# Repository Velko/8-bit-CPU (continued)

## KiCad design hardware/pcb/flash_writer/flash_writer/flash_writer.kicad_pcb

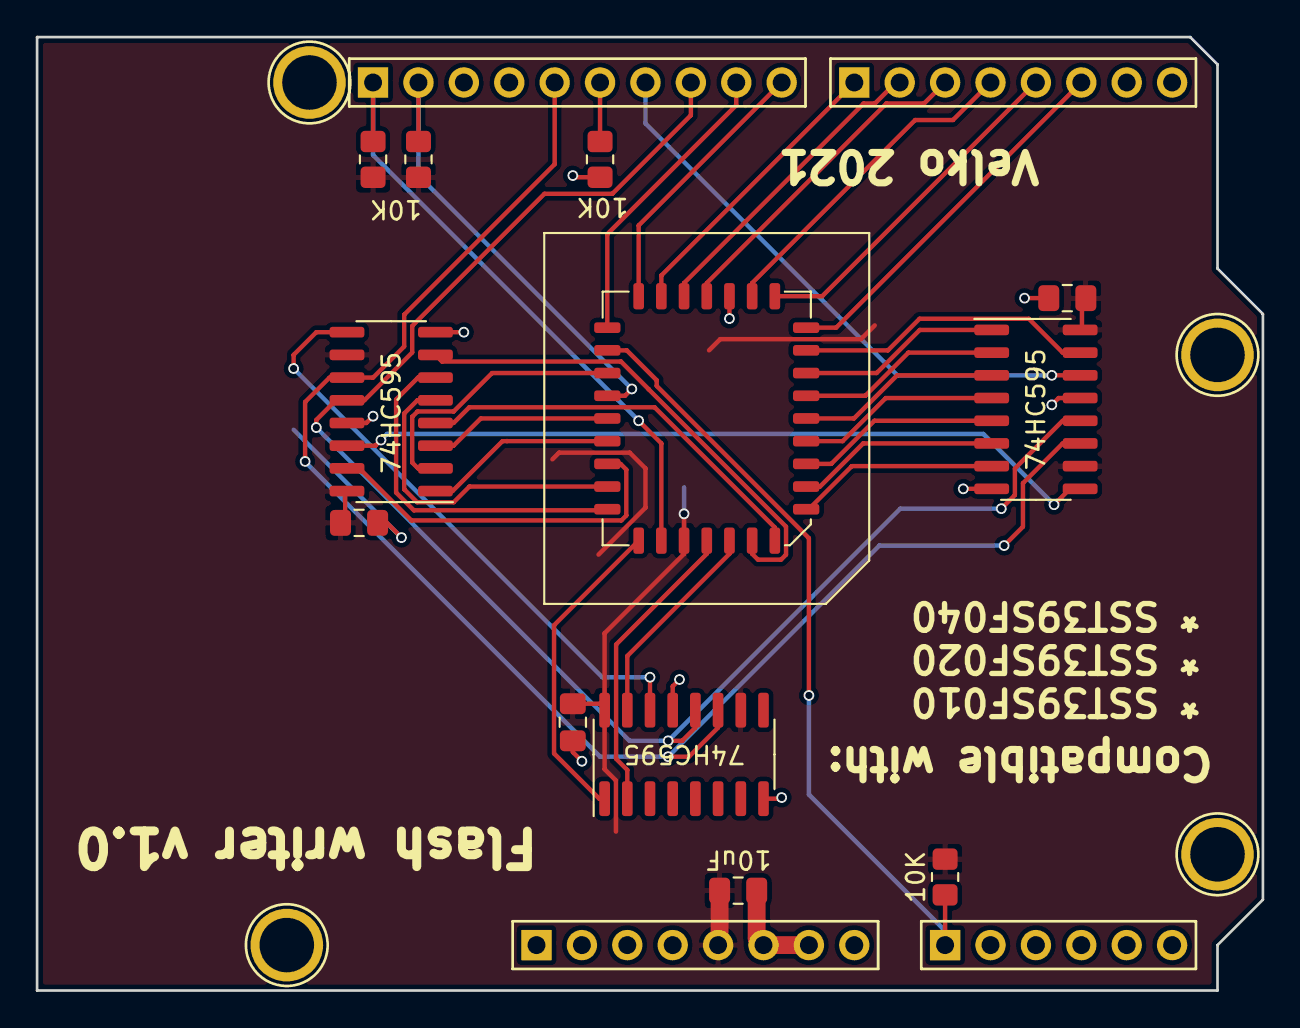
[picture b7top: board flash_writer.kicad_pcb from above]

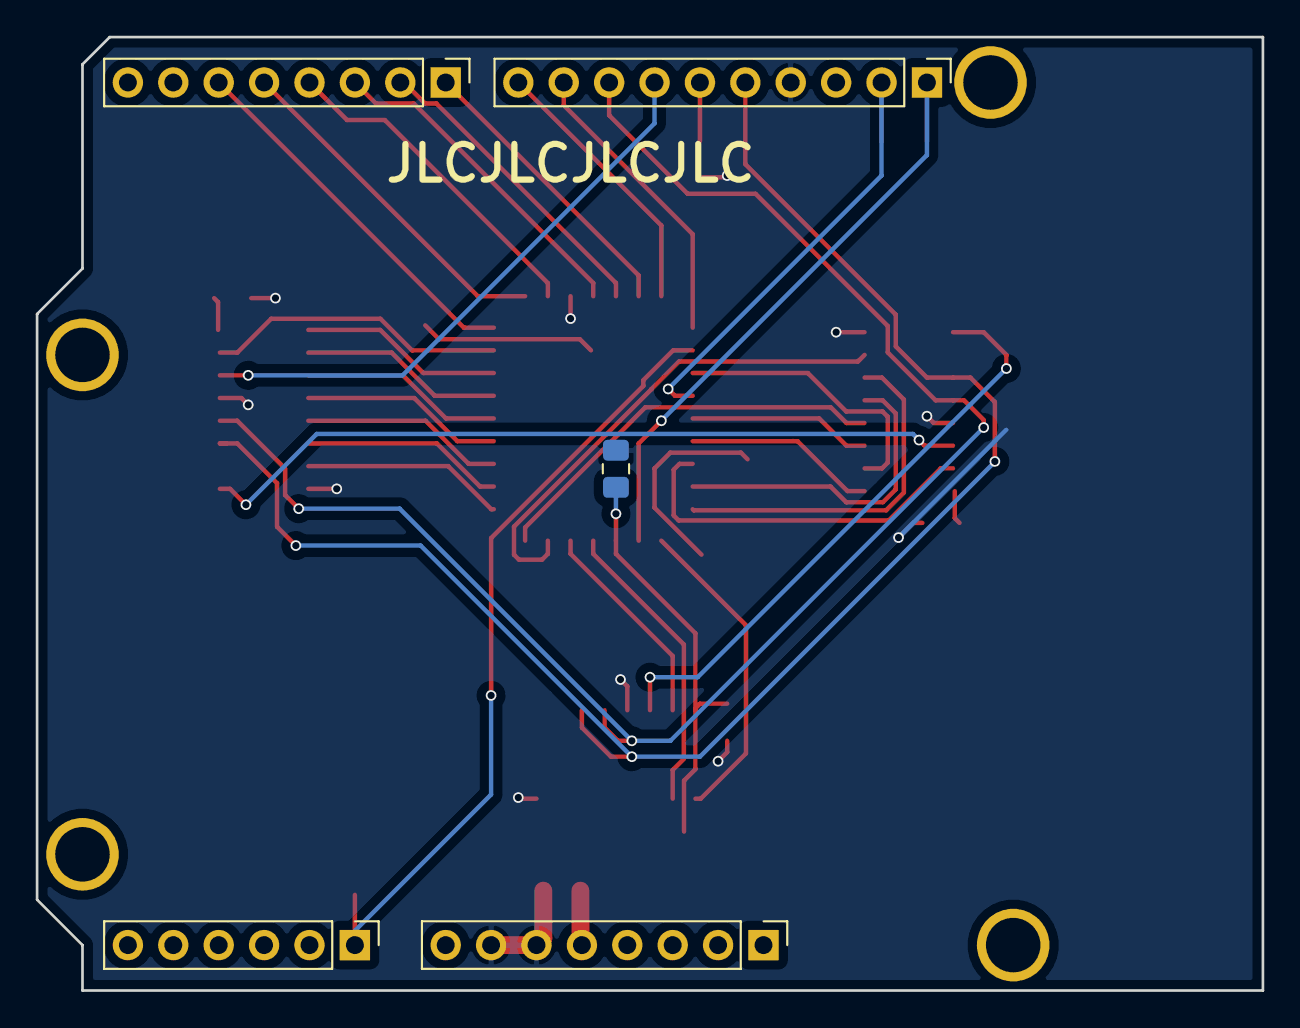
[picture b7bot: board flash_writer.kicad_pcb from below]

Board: 2 copper layers, 68.6 x 53.3 mm, 21 parts (5 on the bottom side), 38 nets.

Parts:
C1, C2, C3, C4: 100nF; C_0805_2012Metric_Pad1.18x1.45mm_HandSolder
C5: 10uF; C_0805_2012Metric_Pad1.18x1.45mm_HandSolder
P1: Power; PinHeader_1x08_P2.54mm_Vertical
P2: Analog; PinHeader_1x06_P2.54mm_Vertical
P3: Digital; PinHeader_1x10_P2.54mm_Vertical
P4: Digital; PinHeader_1x08_P2.54mm_Vertical
P5, P6, P7, P8: CONN_01X01; Arduino_1pin
R1, R2, R3, R4: 10K; R_0805_2012Metric_Pad1.20x1.40mm_HandSolder
U1, U2, U4: 74HC595; SOIC-16_3.9x9.9mm_P1.27mm
U3: SST39SF040; PLCC-32_SMD-Socket

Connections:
+5V: C1.1, C2.1, C3.1, C4.1, C5.1, P1.5, R1.1, R2.1, R4.1, U1.10, U1.16, U2.10, U2.16, U3.32, U4.10, U4.16
A0: U1.15, U3.12
A1: U1.1, U3.11
A2: U1.2, U3.10
A3: U1.3, U3.9
A4: U1.4, U3.8
A5: U1.5, U3.7
A6: U1.6, U3.6
A7: U1.7, U3.5
A8: U2.15, U3.27
A9: U2.1, U3.26
A10: U2.2, U3.23
A11: U2.3, U3.25
A12: U2.4, U3.4
A13: U2.5, U3.28
A14: U2.6, U3.29
A15: U2.7, U3.3
A16: U3.2, U4.15
A17: U3.30, U4.1
A18: U3.1, U4.2
D0: P4.6, U3.13
D1: P4.5, U3.14
D2: P4.4, U3.15
D3: P4.3, U3.17
D4: P4.2, U3.18
D5: P4.1, U3.19
D6: P3.10, U3.20
D7: P3.9, U3.21
GND: C1.2, C2.2, C3.2, C4.2, C5.2, P1.6, P1.7, P3.4, R3.2, U1.8, U1.13, U2.8, U2.13, U3.16, U4.8, U4.13
LATCH: P3.8, U1.12, U2.12, U4.12
MISO: P3.6, R3.1
MOSI: P3.7, U1.14
unnamed: U1.9, U2.14
unnamed: U2.9, U4.14
SCK: P3.5, U1.11, U2.11, U4.11
~CE~: P2.1, R4.2, U3.22
~OE~: P3.2, R1.2, U3.24
~WE~: P3.1, R2.2, U3.31

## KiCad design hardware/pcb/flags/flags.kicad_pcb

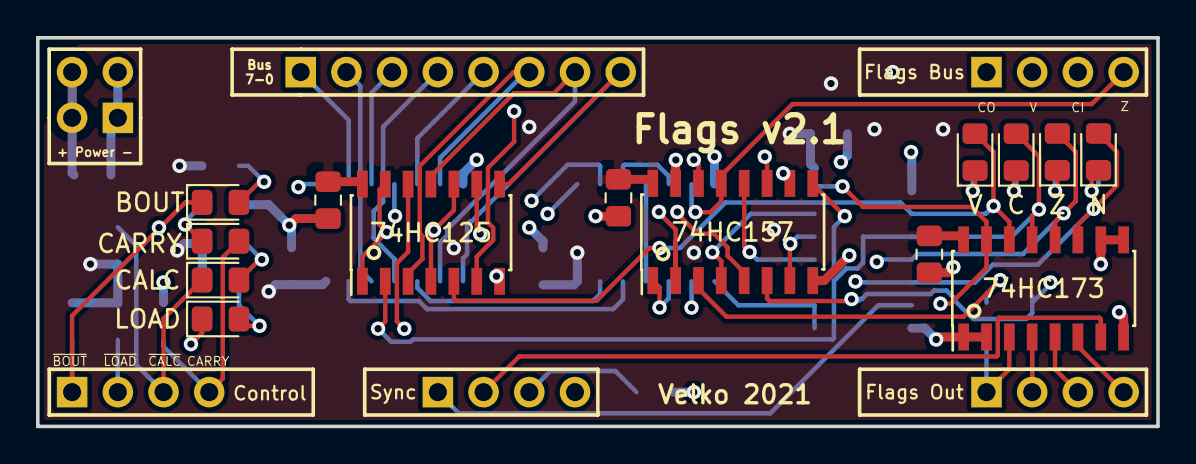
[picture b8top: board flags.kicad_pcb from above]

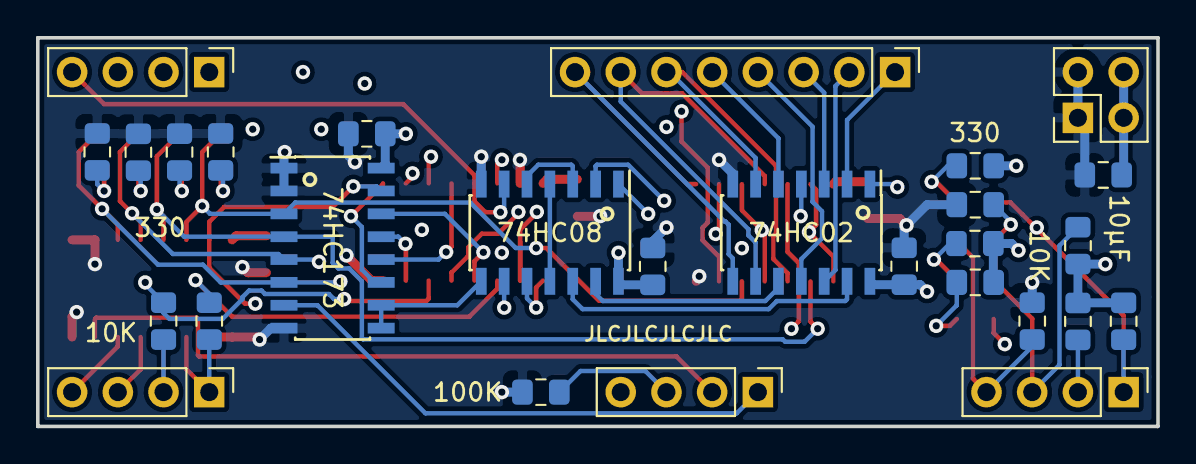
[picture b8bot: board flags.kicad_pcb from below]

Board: 4 copper layers, 62.2 x 21.6 mm, 42 parts (28 on the bottom side), 47 nets.

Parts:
C1, C2, C3, C4, C5, C6: 100nF; C_0805_2012Metric_Pad1.15x1.40mm_HandSolder
C7: 10μF; C_0805_2012Metric_Pad1.15x1.40mm_HandSolder
D1: Z; LED_0805_2012Metric_Pad1.15x1.40mm_HandSolder
D2: V; LED_0805_2012Metric_Pad1.15x1.40mm_HandSolder
D3: N; LED_0805_2012Metric_Pad1.15x1.40mm_HandSolder
D4: C; LED_0805_2012Metric_Pad1.15x1.40mm_HandSolder
D5: LOAD; LED_0805_2012Metric_Pad1.15x1.40mm_HandSolder
D6: BOUT; LED_0805_2012Metric_Pad1.15x1.40mm_HandSolder
D7: CALC; LED_0805_2012Metric_Pad1.15x1.40mm_HandSolder
D8: CARRY; LED_0805_2012Metric_Pad1.15x1.40mm_HandSolder
J1: Bus; PinHeader_1x08_P2.54mm_Vertical
J2: Control; PinHeader_1x04_P2.54mm_Vertical
J3: Sync; PinHeader_1x04_P2.54mm_Vertical
J4: Power; PinHeader_2x02_P2.54mm_Vertical
J5: Flags_Bus; PinHeader_1x04_P2.54mm_Vertical
J6: Ctrl_Out; PinHeader_1x04_P2.54mm_Vertical
R1, R2, R11, R12, R13, R14: 10K; R_0805_2012Metric_Pad1.15x1.40mm_HandSolder
R3, R4, R5, R6, R7, R8, R9, R10: 330; R_0805_2012Metric_Pad1.15x1.40mm_HandSolder
R15: 100K; R_0805_2012Metric_Pad1.15x1.40mm_HandSolder
U1: 74HC02; SOIC-14_3.9x8.7mm_P1.27mm
U2: 74HC08; SOIC-14_3.9x8.7mm_P1.27mm
U3: 74HC157; SOIC-16_3.9x9.9mm_P1.27mm
U4, U5: 74HC173; SOIC-16_3.9x9.9mm_P1.27mm
U6: 74HC125; SOIC-14_3.9x8.7mm_P1.27mm

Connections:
BUS0: J1.8, U1.8, U3.11, U6.8
BUS1: J1.7, U1.9, U3.14, U6.11
BUS2: J1.6, U1.6, U3.5, U6.3
BUS3: J1.5, U1.5, U3.2, U6.6
BUS4: J1.4, U1.11
BUS5: J1.3, U1.3
BUS6: J1.2, U1.12
BUS7: J1.1, U1.2, U3.10
CARRY_IN: J5.3, R1.2, U3.6
CARRY_OUT: D8.2, J2.4, J5.1, R14.2
CLK: J3.1, U4.7
C_CTRL: J6.2, R1.1, U5.4
C_D: D4.2, U4.4, U5.13, U6.2
C_I: U3.7, U4.13
GND: C1.2, C2.2, C3.2, C4.2, C5.2, C6.2, C7.2, J4.1, J4.2, R3.1, R4.1, R5.1, R6.1, R10.1, R14.1, R15.1, U1.7, U2.7, U3.8, U3.15, U4.1, U4.2, U4.8, U5.1, U5.2, U5.8, U5.9, U5.10, U6.7
N_CTRL: J6.4, U5.6
N_D: D3.2, U4.6, U5.11, U6.9
N_I: U3.9, U4.11
unnamed: D1.1, R3.2
unnamed: D2.1, R4.2
unnamed: D3.1, R5.2
unnamed: D4.1, R6.2
unnamed: D5.2, R8.2
unnamed: D6.2, R7.2
unnamed: D7.2, R9.2
unnamed: D8.1, R10.2
unnamed: U1.1, U2.2
unnamed: U1.4, U2.1
unnamed: U1.10, U2.13
unnamed: U1.13, U2.12
unnamed: U2.3, U2.5
unnamed: U2.4, U2.11
OV_IN: J5.2, R2.2, U3.3
RST: J3.3, R15.2, U4.15, U5.15
VCC: C1.1, C2.1, C3.1, C4.1, C5.1, C6.1, C7.1, J4.3, J4.4, R7.1, R8.1, R9.1, R11.1, R12.1, R13.1, U1.14, U2.14, U3.16, U4.16, U5.16, U6.14
V_CTRL: J6.1, R2.1, U5.3
V_D: D2.2, U4.3, U5.14, U6.5
V_I: U3.4, U4.14
Z_CTRL: J6.3, U5.5
Z_D: D1.2, U4.5, U5.12, U6.12
Z_I: U3.12, U4.12
Z_OUT: J5.4, U2.6, U3.13
~B_CALC~: D7.1, J2.3, R13.2, U2.9
~B_LOAD~: D5.1, J2.2, R12.2, U2.10, U3.1
~CLK~: J3.2, U5.7
~LATCH~: U2.8, U4.9, U4.10
~OUT~: D6.1, J2.1, R11.2, U6.1, U6.4, U6.10, U6.13

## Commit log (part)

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2026-05-06 Test Store
2026-05-06 Test indexed load and store
2026-05-06 Simplify the RAM tests
2026-05-06 Mark instructions missing tests
2026-05-06 Move check_pcrel to base module
2026-05-07 Stop previous emulator, if running
2026-05-07 Use API to load program
2026-05-07 Fix assisted stepping
2026-05-07 Centralized register debug formatting
2026-05-07 Step-run a program in debugger
2026-05-11 Porting text output to SDP
2026-05-11 Unify LD instruction variants
2026-05-11 Add LEA TDP
2026-05-11 Get rid of TSTX instruction
2026-05-11 Add missing TDP register
2026-05-11 Port ldx and stx to SDP and TDP-relative operations
2026-05-12 Abstracted UART putc
2026-05-12 Snake - prepare screen
2026-05-12 Add st (TDP++) instruction
2026-05-12 Draw moving snake
2026-05-12 2-way monitor (threaded)
2026-05-12 2-way monitor (singlethread, select)
2026-05-12 Listen keys and echo
2026-05-12 Adjust newlines for Raw mode
2026-05-13 Support non-terminal stdin
2026-05-13 Diagnotics for raw output
2026-05-13 Extra diag when running in Actions
2026-05-13 Check stdin for EOF
2026-05-13 Additional diag output
2026-05-13 Move the head interactively
2026-05-13 Lookup table for key-to-dir
2026-05-13 Some "cleverness" in head movement
2026-05-13 Refactor and document
2026-05-13 Validate turns
2026-05-13 Use character literals
2026-05-13 Add push and pop for SDP and TDP
2026-05-14 Width/Height constants
2026-05-14 Initialize head and tail arena pointers
2026-05-14 Move rowptr-s as part of movement
2026-05-14 Split packets when uploading larger files
2026-05-14 Show control word on commit
2026-05-14 Dynamic client port
2026-05-14 Infinite length snake + collision detection
2026-05-14 Add loading message
2026-05-14 Desired and actual length
2026-05-14 Swap ptr and screen coord calculations
2026-05-14 Erase the tail (buggy)
2026-05-15 Fix the head/tail movements
2026-05-15 Put data in separate bank
2026-05-15 BCD up/down loop
2026-05-15 Double BCD number
2026-05-15 Use BCD encoded screen coordinates
2026-05-15 Cleanup old convert
2026-05-18 Add tst instruction
2026-05-18 Use TST to recalculate flags
2026-05-18 Configurable regsets
2026-05-18 Convert flag-specific instructions to generalized
2026-05-18 Convert repeat to a list
2026-05-18 Standartize reg parameter naming
2026-05-19 Add repeats to args
2026-05-19 Convert instruction generation to arg-scoped repeats
    Barely working version
2026-05-19 Type-annotated version
2026-05-19 Clean up legacy repeat spec
2026-05-19 Small renames, etc.
2026-05-19 Add dedicated xoffsets
2026-05-20 Calculate screen and data X seperately
2026-05-20 Extract the direction decoding
2026-05-20 Change the DIR_* to non-zero values
2026-05-20 Pointer-relative store/load instructions
2026-05-20 Add walls in arena (backend)
2026-05-20 Shutdown gracefully
2026-05-20 Pseudo-random number generator
2026-05-21 Modulo-38 random numbers
2026-05-21 Swap regs to put rnd8 return value in A
2026-05-21 Modulo-38 C reference code
2026-05-22 Put and consume food
2026-05-22 Fix food retry crash
2026-05-27 Create addrmap-s when compiling
2026-05-28 Switch to hex-encoded numbers in messages
2026-05-28 Add synchronization for memory upload messages
2026-05-28 Drop F from OUT message
2026-05-29 Fix LCD emulator
2026-05-29 Port output
2026-05-29 Rework output formatting
2026-05-29 Color LCD output
2026-05-29 Prevent UART read when it is not selected
2026-05-29 Handle FF byte properly
2026-05-29 Use status register to detect input
2026-05-29 Use real CustomAsm to prepare binaries
2026-05-29 Test IO with peripherals
2026-05-29 Test if IO bus contention is fixed
2026-05-29 Send the input in CPUHelper
2026-05-29 Forward input in message mode
2026-06-01 Pause the game
2026-06-01 Textual-based debugger UI skeleton
2026-06-01 Step to file + line
2026-06-01 Refactor address map loader
2026-06-01 Index mappings by file and line and by address
2026-06-01 Map breakpoints to addresses when toggling
2026-06-02 Cleanup code locations via addresses
2026-06-02 Integrate with real backend debugger
2026-06-02 Move to external CSS
2026-06-02 Show register when stepping
2026-06-02 Reset from TUI
2026-06-02 Collect output messages
2026-06-02 Fix if only one source file
2026-06-02 Absolute paths in .addrmap
2026-06-02 Read initial PC
2026-06-02 Upload binary
2026-06-02 Deprecating GTK-based IDE
2026-06-02 Remove unused type stubs
2026-06-03 Color changed regs
2026-06-03 Updated addrmap and symbols extract
2026-06-03 Continue and set/clear real breakpoints
2026-06-03 Filter out multiple reg updates
2026-06-03 Launch tdebug directly
2026-06-03 Update labels
2026-06-03 Fix MyPy issues
2026-06-03 Add some progress
2026-06-04 Rename "serial" to transport
2026-06-04 Register endpoint
2026-06-04 Use endpoints to respond
2026-06-15 Extract some common Arduino routines
2026-06-26 Load Pin config
2026-06-26 Muxes and shared cfg
2026-06-26 Mux and shared pin configs
2026-06-26 Move loader
2026-06-26 Dispatch to Muxes
